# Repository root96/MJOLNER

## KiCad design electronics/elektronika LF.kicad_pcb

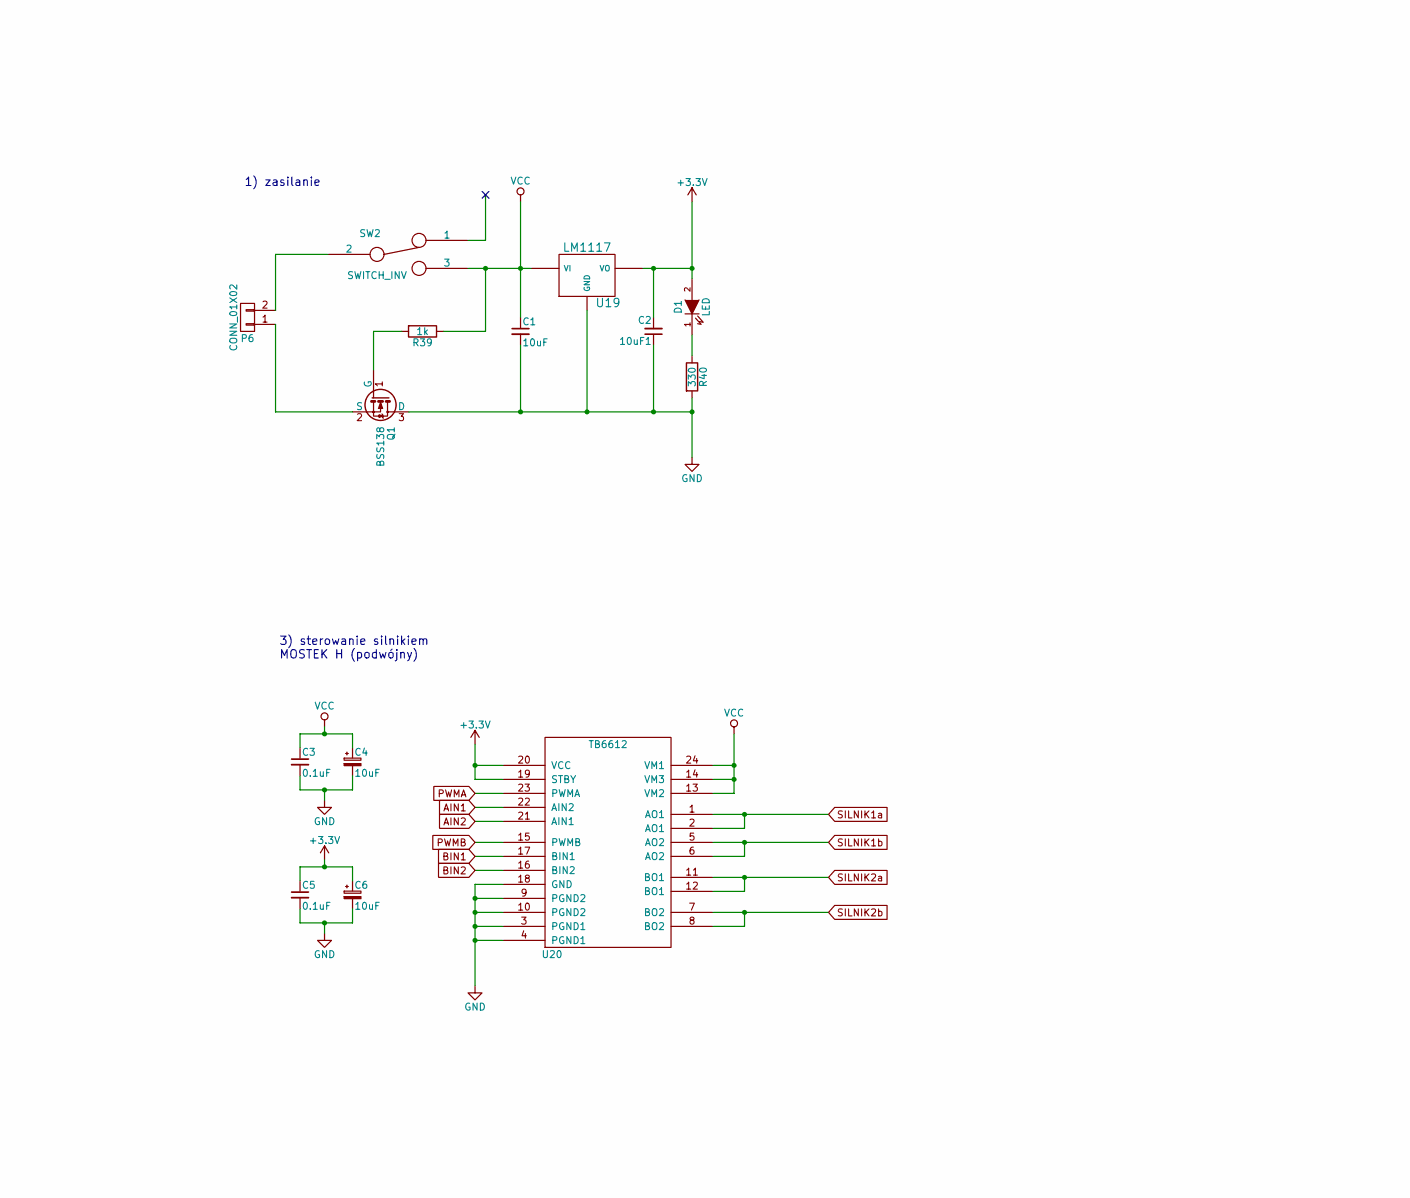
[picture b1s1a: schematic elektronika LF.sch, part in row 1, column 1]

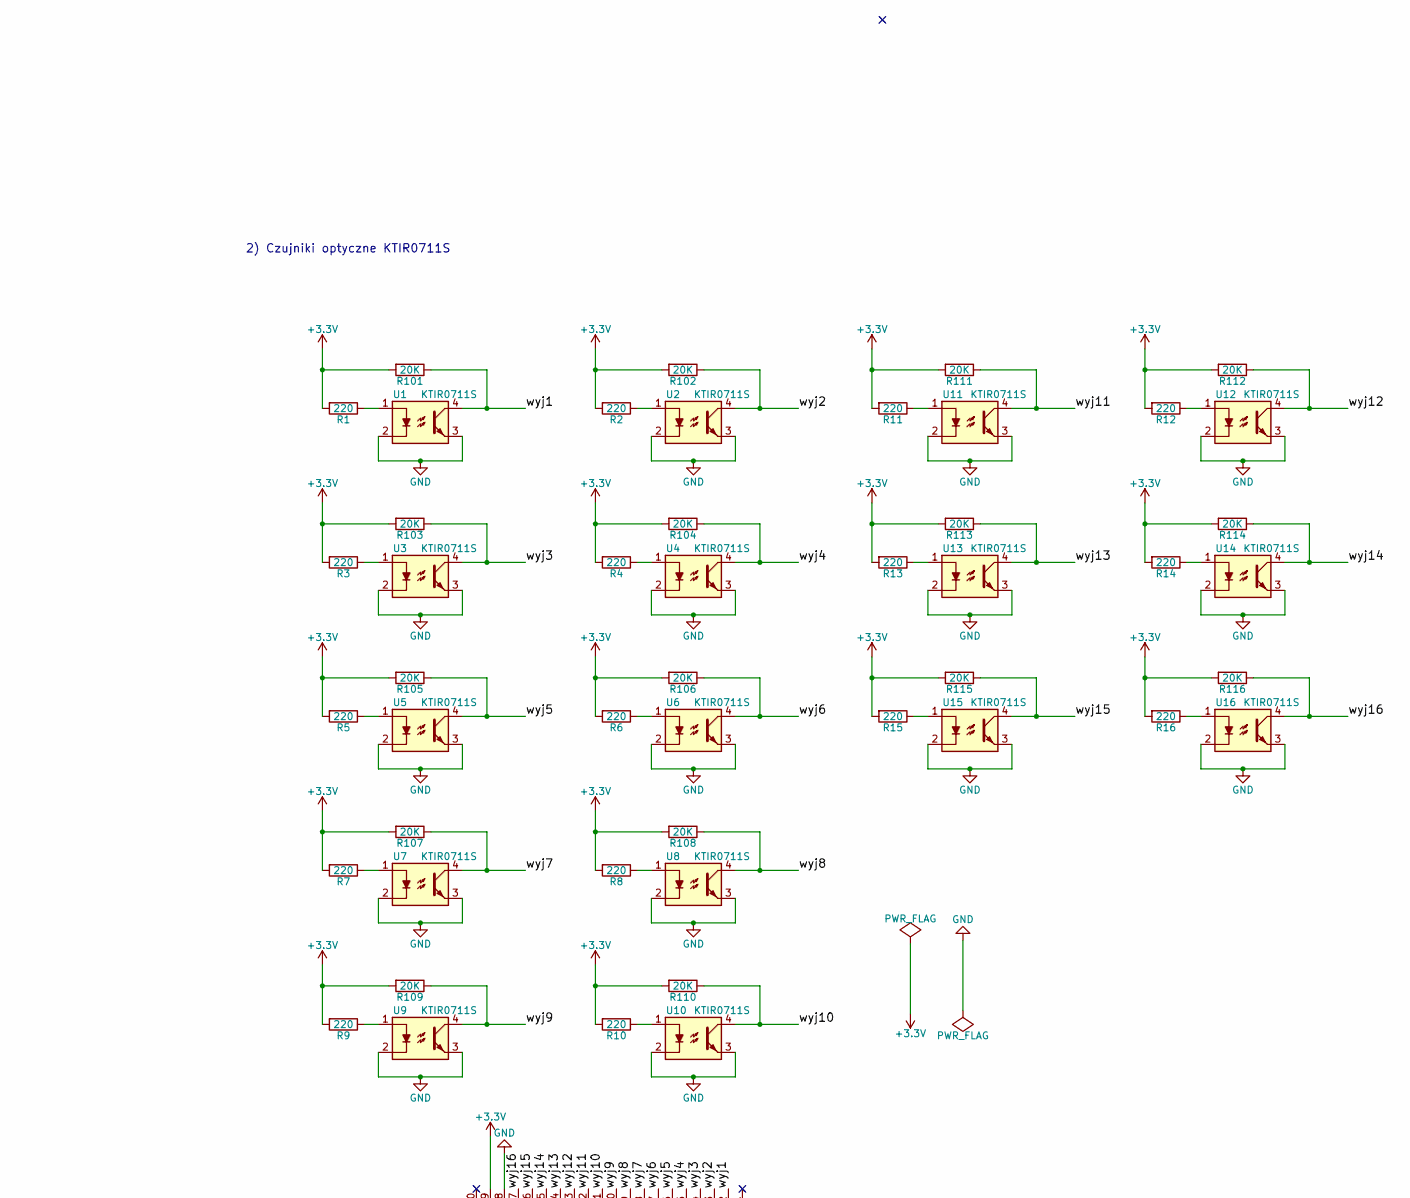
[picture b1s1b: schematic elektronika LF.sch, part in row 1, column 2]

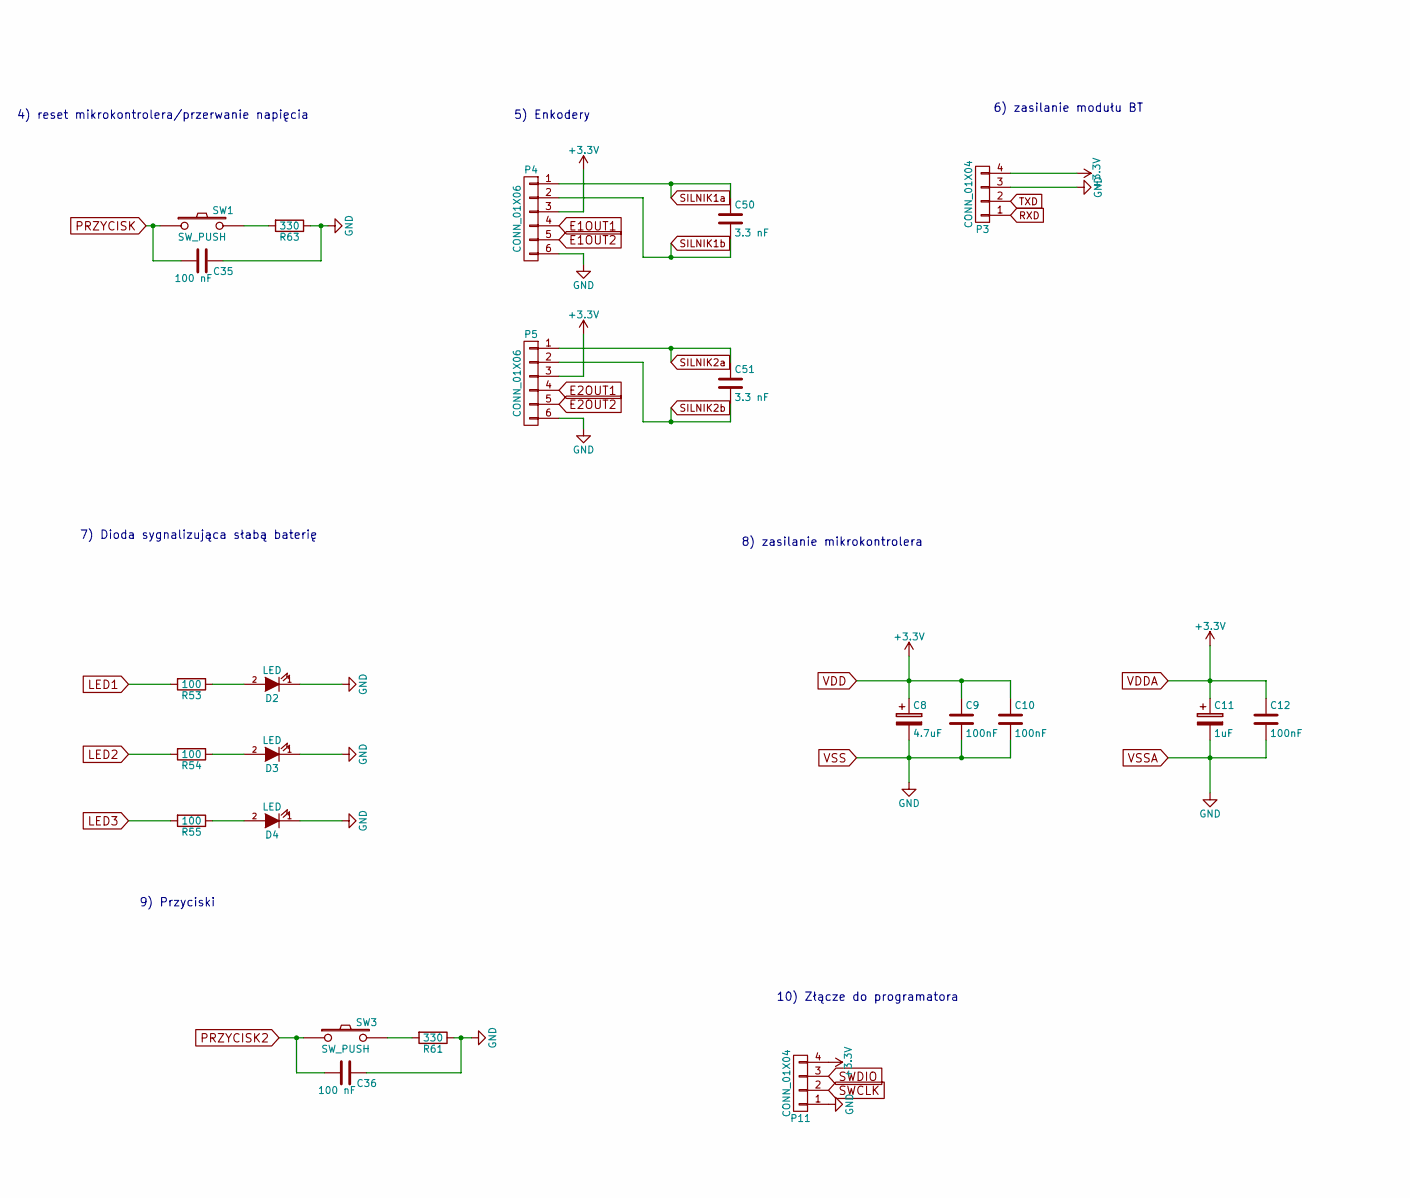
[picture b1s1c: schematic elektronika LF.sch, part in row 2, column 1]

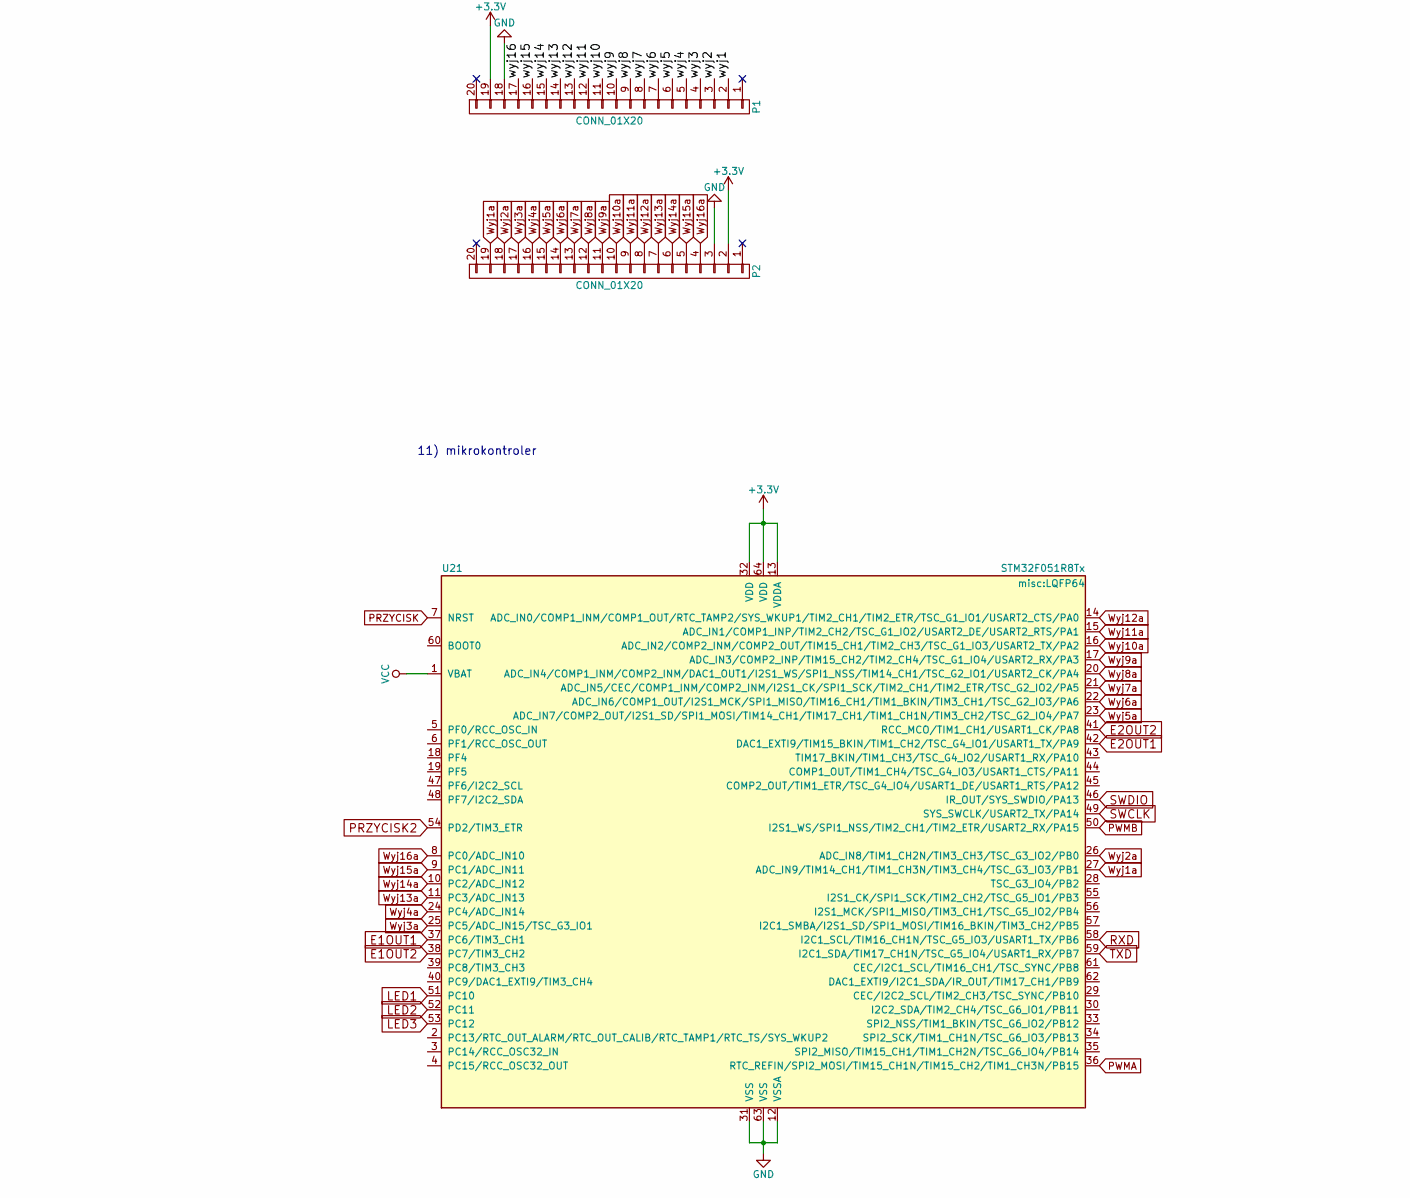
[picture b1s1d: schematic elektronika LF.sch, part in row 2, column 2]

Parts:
10uF1: C2; C_0603
C1, C4, C6: 10uF; C_0603
C3, C5: 0.1uF; C_0603
C8: 4.7uF; C_0603
C9, C10, C12: 100nF; C_0603
C11: 1uF; C_0603
C35, C36: 100 nF; C_0603
C50, C51: 3.3 nF; C_0603
D1, D2, D3, D4: LED; D_0603
P1, P2: CONN_01X20; FCP_ZIF_20
P3, P11: CONN_01X04; Pin_Header_Straight_1x04
P4, P5: CONN_01X06; Pin_Header_Straight_1x06
P6: CONN_01X02; Pin_Header_Straight_1x02
Q1: BSS138; SOT-23
R1, R2, R3, R4, R5, R6, R7, R8, R9, R10, R11, R12, R13, R14, R15, R16: 220; R_0603
R39: 1k; R_0603
R40, R61, R63: 330; R_0603
R53, R54, R55: 100; R_0603
R101, R102, R103, R104, R105, R106, R107, R108, R109, R110, R111, R112, R113, R114, R115, R116: 20K; R_0603
SW1, SW3: SW_PUSH; SW_SPST_FSMSM
SW2: SWITCH_INV; SW_Micro_SPST
U1, U2, U3, U4, U5, U6, U7, U8, U9, U10, U11, U12, U13, U14, U15, U16: KTIR0711S
U19: LM1117; LM1117_SOT223
U20: TB6612
U21: STM32F051R8Tx; LQFP64

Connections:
/wyj1: P1.2, R101.1, U1.4
/wyj2: P1.3, R102.1, U2.4
/wyj3: P1.4, R103.1, U3.4
/wyj4: P1.5, R104.1, U4.4
/wyj5: P1.6, R105.1, U5.4
/wyj6: P1.7, R106.1, U6.4
/wyj7: P1.8, R107.1, U7.4
/wyj8: P1.9, R108.1, U8.4
/wyj9: P1.10, R109.1, U9.4
/wyj10: P1.11, R110.1, U10.4
/wyj11: P1.12, R111.1, U11.4
/wyj12: P1.13, R112.1, U12.4
/wyj13: P1.14, R113.1, U13.4
/wyj14: P1.15, R114.1, U14.4
/wyj15: P1.16, R115.1, U15.4
/wyj16: P1.17, R116.1, U16.4
E1OUT1: P4.4, U21.37 (PC6/TIM3_CH1)
E1OUT2: P4.5, U21.38 (PC7/TIM3_CH2)
E2OUT1: P5.4, U21.42 (DAC1_EXTI9/TIM15_BKIN/TIM1_CH2/TSC_G4_I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)
E2OUT2: P5.5, U21.41 (RCC_MCO/TIM1_CH1/USART1_CK/PA8)
LED1: R53.2, U21.51 (PC10)
LED2: R54.2, U21.52 (PC11)
LED3: R55.2, U21.53 (PC12)
unnamed: D1.1 (K), R40.1
unnamed: D2.2 (A), R53.1
unnamed: D3.2 (A), R54.1
unnamed: D4.2 (A), R55.1
unnamed: P6.1, Q1.2 (S)
unnamed: P6.2, SW2.2
unnamed: Q1.1 (G), R39.2
unnamed: R1.1, U1.1
unnamed: R2.1, U2.1
unnamed: R3.1, U3.1
unnamed: R4.1, U4.1
unnamed: R5.1, U5.1
unnamed: R6.1, U6.1
unnamed: R7.1, U7.1
unnamed: R8.1, U8.1
unnamed: R9.1, U9.1
unnamed: R10.1, U10.1
unnamed: R11.1, U11.1
unnamed: R12.1, U12.1
unnamed: R13.1, U13.1
unnamed: R14.1, U14.1
unnamed: R15.1, U15.1
unnamed: R16.1, U16.1
unnamed: R61.2, SW3.2
unnamed: R63.2, SW1.2
PRZYCISK: C35.2, SW1.1, U21.7 (NRST)
PRZYCISK2: C36.2, SW3.1, U21.54 (PD2/TIM3_ETR)
PWMA: U20.23 (PWMA), U21.36 (RTC_REFIN/SPI2_MOSI/TIM15_CH1N/TIM15_CH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)
PWMB: U20.15 (PWMB), U21.50 (I2S1_WS/SPI1_NSS/TIM2_CH1/TIM2_ETR/USAR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)
RXD: P3.1, U21.58 (I2C1_SCL/TIM16_CH1N/TSC_G5_IO3/USART1_T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)
SILNIK1a: C50.1, P4.1, U20.1 (AO1), U20.2 (AO1)
SILNIK1b: C50.2, P4.2, U20.5 (AO2), U20.6 (AO2)
SILNIK2a: C51.1, P5.1, U20.11 (BO1), U20.12 (BO1)
SILNIK2b: C51.2, P5.2, U20.7 (BO2), U20.8 (BO2)
SWCLK: P11.2, U21.49 (SYS_SWCLK/USART2_TX/PA14)
SWDIO: P11.3, U21.46 (IR_OUT/SYS_SWDIO/PA13)
TXD: P3.2, U21.59 (I2C1_SDA/TIM17_CH1N/TSC_G5_IO4/USART1_R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)
VCC: C1.1, C3.1, C4.1, R39.1, SW2.3, U19.1 (VI), U20.13 (VM2), U20.14 (VM3), U20.24 (VM1), U21.1 (VBAT)
VDD: 10uF1.2, C5.1, C6.1, C8.1, C9.1, C10.1, C11.1, C12.1, D1.2 (A), P1.19, P2.2, P3.4, P4.3, P5.3, P11.4, R1.2, R2.2, R3.2, R4.2, R5.2, R6.2, R7.2, R8.2, R9.2, R10.2, R11.2, R12.2, R13.2, R14.2, R15.2, R16.2, R101.2, R102.2, R103.2, R104.2, R105.2, R106.2, R107.2, R108.2, R109.2, R110.2, R111.2, R112.2, R113.2, R114.2, R115.2, R116.2, U19.2 (VO), U20.19 (STBY), U20.20 (VCC), U21.13 (VDDA), U21.32 (VDD), U21.64 (VDD)
VSS: 10uF1.1, C1.2, C3.2, C4.2, C5.2, C6.2, C8.2, C9.2, C10.2, C11.2, C12.2, C35.1, C36.1, D2.1 (K), D3.1 (K), D4.1 (K), P1.18, P2.3, P3.3, P4.6, P5.6, P11.1, Q1.3 (D), R40.2, R61.1, R63.1, U1.2, U1.3, U2.2, U2.3, U3.2, U3.3, U4.2, U4.3, U5.2, U5.3, U6.2, U6.3, U7.2, U7.3, U8.2, U8.3, U9.2, U9.3, U10.2, U10.3, U11.2, U11.3, U12.2, U12.3, U13.2, U13.3, U14.2, U14.3, U15.2, U15.3, U16.2, U16.3, U19.3 (GND), U20.3 (PGND1), U20.4 (PGND1), U20.9 (PGND2), U20.10 (PGND2), U20.18 (GND), U21.12 (VSSA), U21.31 (VSS), U21.63 (VSS)
Wyj1a: P2.19, U21.27 (ADC_IN9/TIM14_CH1/TIM1_CH3N/TIM3_CH4/TS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)
Wyj2a: P2.18, U21.26 (ADC_IN8/TIM1_CH2N/TIM3_CH3/TSC_G3_IO2/P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)
Wyj3a: P2.17, U21.25 (PC5/ADC_IN15/TSC_G3_IO1)
Wyj4a: P2.16, U21.24 (PC4/ADC_IN14)
Wyj5a: P2.15, U21.23 (ADC_IN7/COMP2_OUT/I2S1_SD/SPI1_MOSI/TIM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)
Wyj6a: P2.14, U21.22 (ADC_IN6/COMP1_OUT/I2S1_MCK/SPI1_MISO/TI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)
Wyj7a: P2.13, U21.21 (ADC_IN5/CEC/COMP1_INM/COMP2_INM/I2S1_CK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)
Wyj8a: P2.12, U21.20 (ADC_IN4/COMP1_INM/COMP2_INM/DAC1_OUT1/I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)
Wyj9a: P2.11, U21.17 (ADC_IN3/COMP2_INP/TIM15_CH2/TIM2_CH4/TS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)
Wyj10a: P2.10, U21.16 (ADC_IN2/COMP2_INM/COMP2_OUT/TIM15_CH1/T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)
Wyj11a: P2.9, U21.15 (ADC_IN1/COMP1_INP/TIM2_CH2/TSC_G1_IO2/U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)
Wyj12a: P2.8, U21.14 (ADC_IN0/COMP1_INM/COMP1_OUT/RTC_TAMP2/S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)
Wyj13a: P2.7, U21.11 (PC3/ADC_IN13)
Wyj14a: P2.6, U21.10 (PC2/ADC_IN12)
Wyj15a: P2.5, U21.9 (PC1/ADC_IN11)
Wyj16a: P2.4, U21.8 (PC0/ADC_IN10)

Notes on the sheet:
1) zasilanie
3) sterowanie silnikiem MOSTEK H (podwójny)
11) mikrokontroler
8) zasilanie mikrokontrolera
2) Czujniki optyczne KTIR0711S
4) reset mikrokontrolera/przerwanie napięcia
6) zasilanie modułu BT
7) Dioda sygnalizująca słabą baterię
5) Enkodery
9) Przyciski
10) Złącze do programatora

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
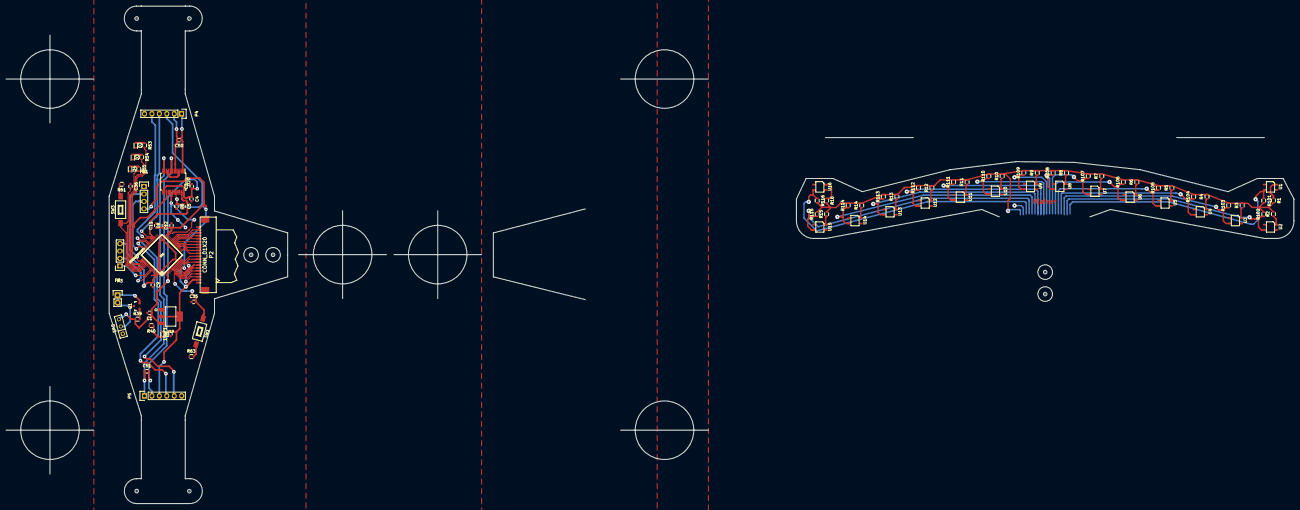
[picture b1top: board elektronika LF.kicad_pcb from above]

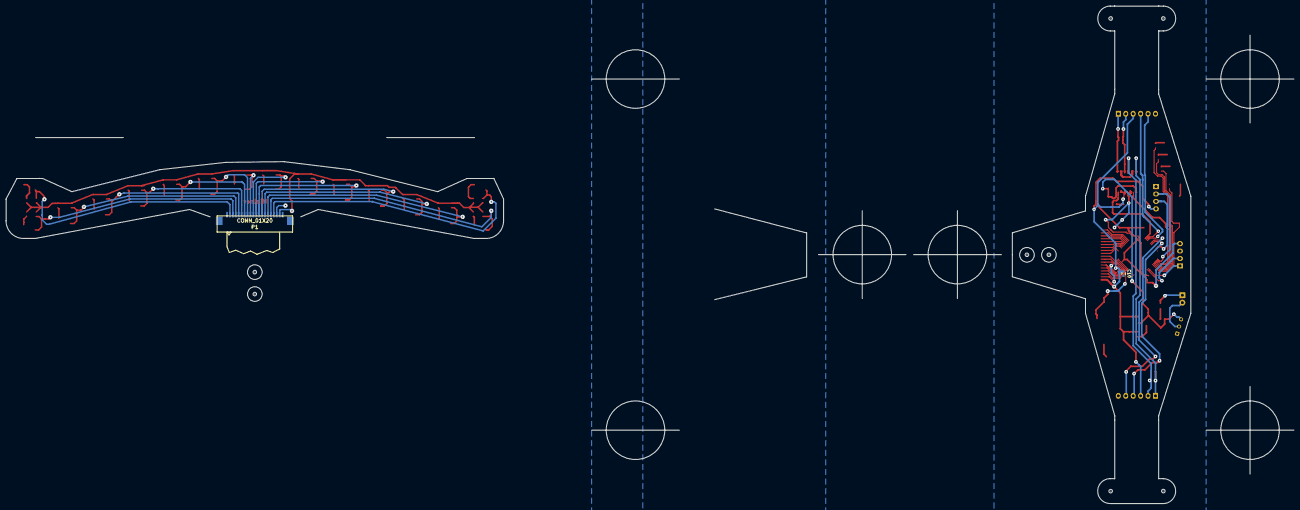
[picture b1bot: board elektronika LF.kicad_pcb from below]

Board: 2 copper layers, 440.1 x 170.0 mm, 88 parts (2 on the bottom side), 81 nets.

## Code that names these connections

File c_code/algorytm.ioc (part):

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Mcu.Name=STM32F051R8Tx
Mcu.Package=LQFP64
Mcu.UserName=STM32F051R8Tx
PA0.GPIOParameters=GPIO_Label
PA0.GPIO_Label=Wyj12a
PA0.Mode=IN0
PA0.Signal=ADC_IN0
PA1.GPIOParameters=GPIO_Label
PA1.GPIO_Label=Wyj11a
PA1.Mode=IN1
PA1.Signal=ADC_IN1
PA11.GPIOParameters=GPIO_Label
PA11.GPIO_Label=BIN2
PA11.Signal=GPIO_Output
PA13.Mode=Serial_Wire
PA13.Signal=SYS_SWDIO
PA14.Mode=Serial_Wire
PA14.Signal=SYS_SWCLK
PA15.GPIOParameters=GPIO_Label
PA15.GPIO_Label=PWMB
PA15.Signal=S_TIM2_CH1_ETR
PA2.GPIOParameters=GPIO_Label
PA2.GPIO_Label=Wyj10a
PA2.Mode=IN2
PA2.Signal=ADC_IN2
PA3.GPIOParameters=GPIO_Label
PA3.GPIO_Label=Wyj9a
PA3.Mode=IN3
PA3.Signal=ADC_IN3
PA4.GPIOParameters=GPIO_Label
PA4.GPIO_Label=Wyj8a
PA4.Mode=IN4
PA4.Signal=ADC_IN4
PA5.GPIOParameters=GPIO_Label
PA5.GPIO_Label=Wyj7a
PA5.Mode=IN5
PA5.Signal=ADC_IN5
PA6.GPIOParameters=GPIO_Label
PA6.GPIO_Label=Wyj6a
PA6.Mode=IN6
PA6.Signal=ADC_IN6
PA7.GPIOParameters=GPIO_Label
PA7.GPIO_Label=Wyj5a
PA7.Mode=IN7
PA7.Signal=ADC_IN7
PB0.GPIOParameters=GPIO_Label
PB0.GPIO_Label=Wyj2a
PB0.Mode=IN8
PB0.Signal=ADC_IN8
PB1.GPIOParameters=GPIO_Label
PB1.GPIO_Label=Wyj1a
PB1.Mode=IN9
PB1.Signal=ADC_IN9
PB10.GPIOParameters=GPIO_Label
PB10.GPIO_Label=AIN1
PB10.Signal=GPIO_Output
PB14.GPIOParameters=GPIO_Label
PB14.GPIO_Label=AIN2
PB14.Signal=GPIO_Output
PB15.GPIOParameters=GPIO_Label
PB15.GPIO_Label=PWMA
PB15.Signal=S_TIM15_CH2
PB6.GPIOParameters=GPIO_Label
PB6.GPIO_Label=RXD
PB6.Mode=Asynchronous
PB6.Signal=USART1_TX
PB7.GPIOParameters=GPIO_Label
PB7.GPIO_Label=TXD
PB7.Mode=Asynchronous
PB7.Signal=USART1_RX
PC0.GPIOParameters=GPIO_Label
PC0.GPIO_Label=Wyj16a
PC0.Mode=IN10
PC0.Signal=ADC_IN10
PC1.GPIOParameters=GPIO_Label
PC1.GPIO_Label=Wyj15a
PC1.Mode=IN11
PC1.Signal=ADC_IN11
PC10.GPIOParameters=GPIO_Label
PC10.GPIO_Label=LED1
PC10.Signal=GPIO_Output
PC11.GPIOParameters=GPIO_Label
PC11.GPIO_Label=LED2
PC11.Signal=GPIO_Output
PC12.GPIOParameters=GPIO_Label
PC12.GPIO_Label=LED3
PC12.Signal=GPIO_Output
PC2.GPIOParameters=GPIO_Label
PC2.GPIO_Label=Wyj14a
PC2.Mode=IN12
PC2.Signal=ADC_IN12
PC3.GPIOParameters=GPIO_Label
PC3.GPIO_Label=Wyj13a
PC3.Mode=IN13
PC3.Signal=ADC_IN13
PC4.GPIOParameters=GPIO_Label
PC4.GPIO_Label=Wyj4a
PC4.Mode=IN14
PC4.Signal=ADC_IN14
PC5.GPIOParameters=GPIO_Label
PC5.GPIO_Label=Wyj3a
PC5.Mode=IN15
PC5.Signal=ADC_IN15
PC9.GPIOParameters=GPIO_Label
PC9.GPIO_Label=BIN1
PC9.Signal=GPIO_Output
PD2.GPIOParameters=GPIO_Label
PD2.GPIO_Label=PRZYCISK2
PD2.Signal=GPIO_Input
RCC.SYSCLKFreq_VALUE=48000000
RCC.SYSCLKSource=RCC_SYSCLKSOURCE_PLLCLK
board=algorytm

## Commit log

2018-03-30 inital commit
